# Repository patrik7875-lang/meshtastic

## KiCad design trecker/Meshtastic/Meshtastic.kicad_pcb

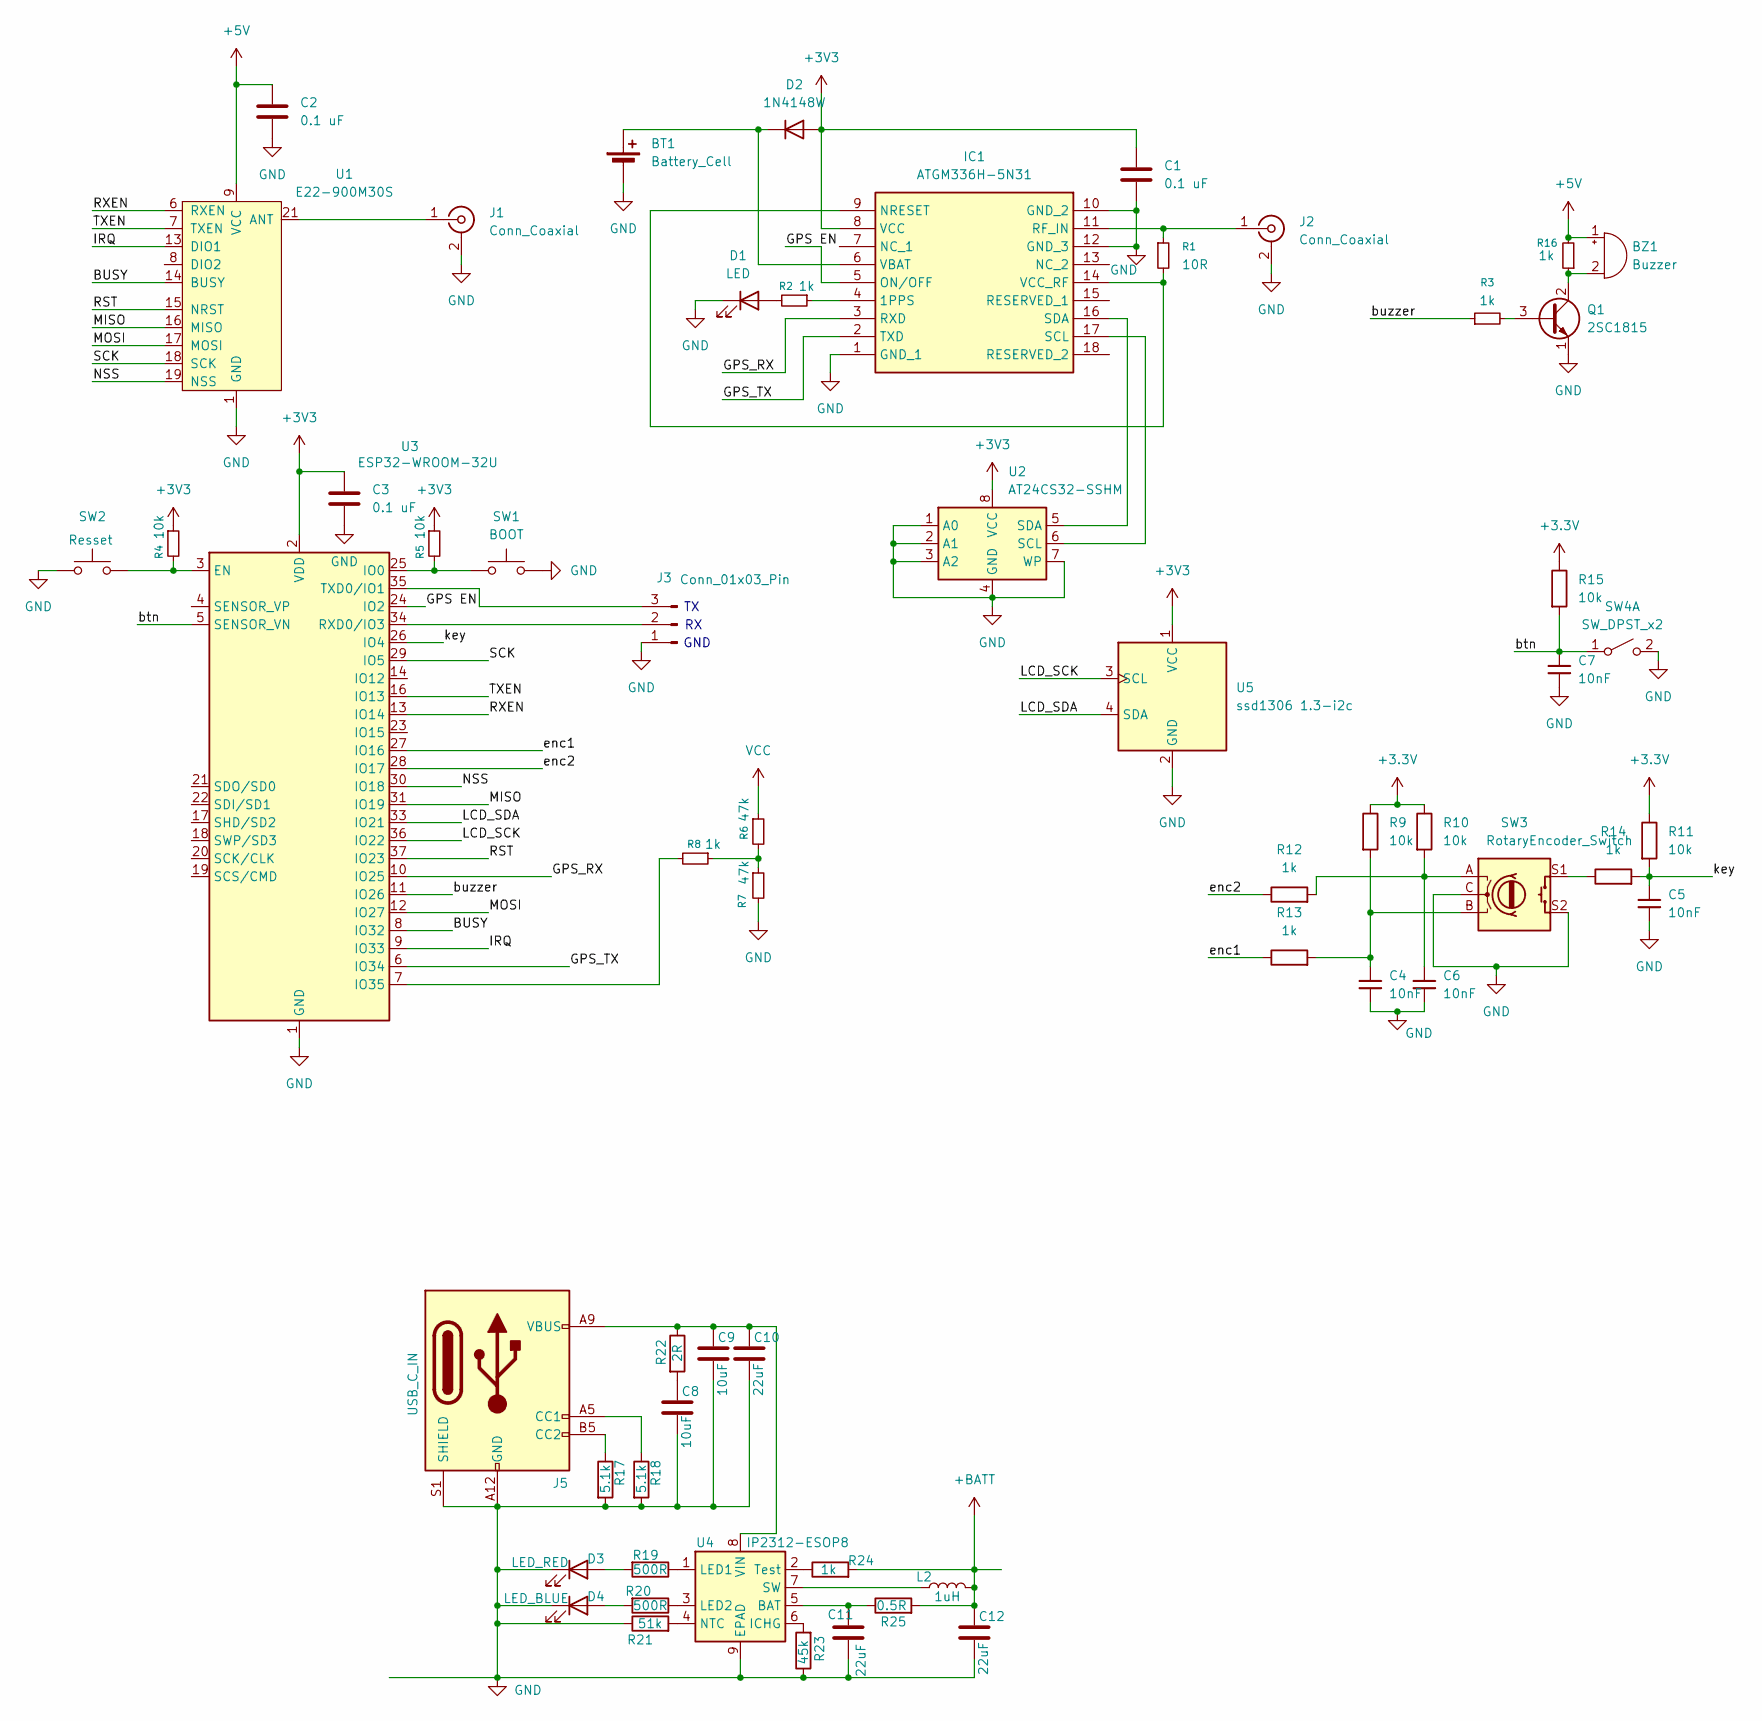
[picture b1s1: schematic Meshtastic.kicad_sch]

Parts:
BT1: Battery_Cell; BatteryHolder_Keystone_3001_1x12mm
BZ1: Buzzer; Buzzer_Murata_PKMCS0909E
C1, C2, C3: 0.1 uF; LED_0805_2012Metric
C4, C5, C6, C7: 10nF; C_0805_2012Metric
C8, C9: 10uF; C_0805_2012Metric_Pad1.18x1.45mm_HandSolder
C10, C11, C12: 22uF; C_0805_2012Metric_Pad1.18x1.45mm_HandSolder
D1: LED; LED_0805_2012Metric
D2: 1N4148W; D_SOD-123
D3: LED_RED; LED_0805_2012Metric_Pad1.15x1.40mm_HandSolder
D4: LED_BLUE; LED_0805_2012Metric_Pad1.15x1.40mm_HandSolder
IC1: ATGM336H-5N31; ATGM336H5N31; Manufacturer_Part_Number ATGM336H-5N31
J1: Conn_Coaxial; SMA_Molex_73251-2200_Horizontal
J2: Conn_Coaxial; U.FL_Hirose_U.FL-R-SMT-1_Vertical
J3: Conn_01x03_Pin; PinHeader_1x03_P2.00mm_Vertical
J5: USB_C_IN; USB_C_Receptacle_GCT_USB4125-xx-x_6P_TopMnt_Horizontal
L2: 1uH; L_Coilcraft_XxL4030
Q1: 2SC1815; TSOT-23
R1: 10R; C_0805_2012Metric
R2, R3, R8, R16: 1k; C_0805_2012Metric
R4, R5: 10k; C_0805_2012Metric
R6, R7: 47k; C_0805_2012Metric
R9, R10, R11, R15: 10k; R_0805_2012Metric
R12, R13, R14: 1k; R_0805_2012Metric
R17, R18: 5.1k; R_0805_2012Metric_Pad1.20x1.40mm_HandSolder
R19, R20: 500R; R_0805_2012Metric_Pad1.20x1.40mm_HandSolder
R21: 51k; R_0805_2012Metric_Pad1.20x1.40mm_HandSolder
R22: 2R; R_0805_2012Metric_Pad1.20x1.40mm_HandSolder
R23: 45k; R_0805_2012Metric_Pad1.20x1.40mm_HandSolder
R24: 1k; R_0805_2012Metric_Pad1.20x1.40mm_HandSolder
R25: 0.5R; R_0805_2012Metric_Pad1.20x1.40mm_HandSolder
SW1: BOOT; SW_SPST_B3U-1000P
SW2: Resset; SW_SPST_B3U-1000P
SW3: RotaryEncoder_Switch; RotaryEncoder_EC11B-Horizontal-Dual
SW4: SW_DPST_x2; SW_Tactile_SPST_Angled_PTS645Vx39-2LFS
U1: E22-900M30S; e22-900m30s-handsoldering; LCSC# C411294
U2: AT24CS32-SSHM; SOIC-8_3.9x4.9mm_P1.27mm
U3: ESP32-WROOM-32U; ESP32-WROOM-32D
U4: IP2312-ESOP8; SOIC-8-1EP_3.9x4.9mm_P1.27mm_EP2.41x3.3mm_ThermalVias
U5: ssd1306 1.3-i2c; Display_128x64_1,3_I2C

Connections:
+3.3V: R9.1, R10.1, R11.1, R15.1
+3V3: C1.1, C3.2, D2.2 (A), IC1.8 (VCC), R4.1, R5.1, U2.8 (VCC), U3.2 (VDD), U5.1 (VCC)
+BATT: C12.1, L2.2, R24.2, R25.2
/BUSY: U1.14 (BUSY), U3.8 (IO32)
/GPS EN: IC1.5 (ON/OFF), U3.24 (IO2)
/GPS_RX: IC1.3 (RXD), U3.10 (IO25)
/GPS_TX: IC1.2 (TXD), U3.6 (IO34)
/IRQ: U1.13 (DIO1), U3.9 (IO33)
/LCD_SCK: U3.36 (IO22), U5.3 (SCL)
/LCD_SDA: U3.33 (IO21), U5.4 (SDA)
/MISO: U1.16 (MISO), U3.31 (IO19)
/MOSI: U1.17 (MOSI), U3.12 (IO27)
/NSS: U1.19 (NSS), U3.30 (IO18)
/RST: U1.15 (NRST), U3.37 (IO23)
/RXEN: U1.6 (RXEN), U3.13 (IO14)
/SCK: U1.18 (SCK), U3.29 (IO5)
/TXEN: U1.7 (TXEN), U3.16 (IO13)
/btn: C7.1, R15.2, SW4.1 (A), U3.5 (SENSOR_VN)
/buzzer: R3.1, U3.11 (IO26)
/enc1: R13.1, U3.27 (IO16)
/enc2: R12.1, U3.28 (IO17)
/key: C5.1, R11.2, R14.2, U3.26 (IO4)
GND: BT1.2 (-), C1.2, C2.1, C3.1, C4.2, C5.2, C6.2, C7.2, C8.2, C9.2, C10.2, C11.2, C12.2, D1.1 (K), D3.1 (K), D4.1 (K), IC1.1 (GND_1), IC1.10 (GND_2), IC1.12 (GND_3), J1.2 (Ext), J2.2 (Ext), J3.1, J5.A12 (GND), J5.B12 (GND), J5.S1 (SHIELD), Q1.1 (E), R7.2, R17.2, R18.2, R21.1, R23.1, SW1.2, SW2.1, SW3.C, SW3.S2, SW4.2 (B), U1.1 (GND), U1.2 (GND), U1.3 (GND), U1.4 (GND), U1.5 (GND), U1.11 (GND), U1.12 (GND), U1.20 (GND), U1.22 (GND), U2.1 (A0), U2.2 (A1), U2.3 (A2), U2.4 (GND), U2.7 (WP), U3.1 (GND), U3.15 (GND), U3.38 (GND), U3.39 (GND), U4.9 (EPAD), U5.2 (GND)
unnamed: BT1.1 (+), D2.1 (K), IC1.6 (VBAT)
unnamed: BZ1.2 (-), Q1.2 (C), R16.1
unnamed: C4.1, R9.2, R13.2, SW3.B
unnamed: C6.1, R10.2, R12.2, SW3.A
unnamed: C8.1, R22.2
unnamed: D1.2 (A), R2.2
unnamed: D3.2 (A), R19.2
unnamed: D4.2 (A), R20.2
unnamed: IC1.4 (1PPS), R2.1
unnamed: IC1.9 (NRESET), IC1.14 (VCC_RF), R1.2
unnamed: IC1.11 (RF_IN), J2.1 (In), R1.1
unnamed: IC1.17 (SCL), U2.6 (SCL)
unnamed: IC1.16 (SDA), U2.5 (SDA)
unnamed: J1.1 (In), U1.21 (ANT)
unnamed: J3.2, U3.34 (RXD0/IO3)
unnamed: J3.3, U3.35 (TXD0/IO1)
unnamed: J5.A5 (CC1), R18.1
unnamed: J5.B5 (CC2), R17.1
unnamed: Q1.3 (B), R3.2
unnamed: R6.2, R7.1, R8.1
unnamed: R14.1, SW3.S1
unnamed: R4.2, SW2.2, U3.3 (EN)
unnamed: R5.2, SW1.1, U3.25 (IO0)
unnamed: R8.2, U3.7 (IO35)
unnamed: C11.1, R25.1, U4.5 (BAT)
unnamed: R23.2, U4.6 (ICHG)
unnamed: R19.1, U4.1 (LED1)
unnamed: R20.1, U4.3 (LED2)
unnamed: R21.2, U4.4 (NTC)
unnamed: L2.1, U4.7 (SW)
unnamed: R24.1, U4.2 (Test)
unnamed: C9.1, C10.1, J5.A9 (VBUS), J5.B9 (VBUS), R22.1, U4.8 (VIN)

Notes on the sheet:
GND

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
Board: 2 copper layers, 59 parts (6 on the bottom side), 56 nets, no tracks yet.
